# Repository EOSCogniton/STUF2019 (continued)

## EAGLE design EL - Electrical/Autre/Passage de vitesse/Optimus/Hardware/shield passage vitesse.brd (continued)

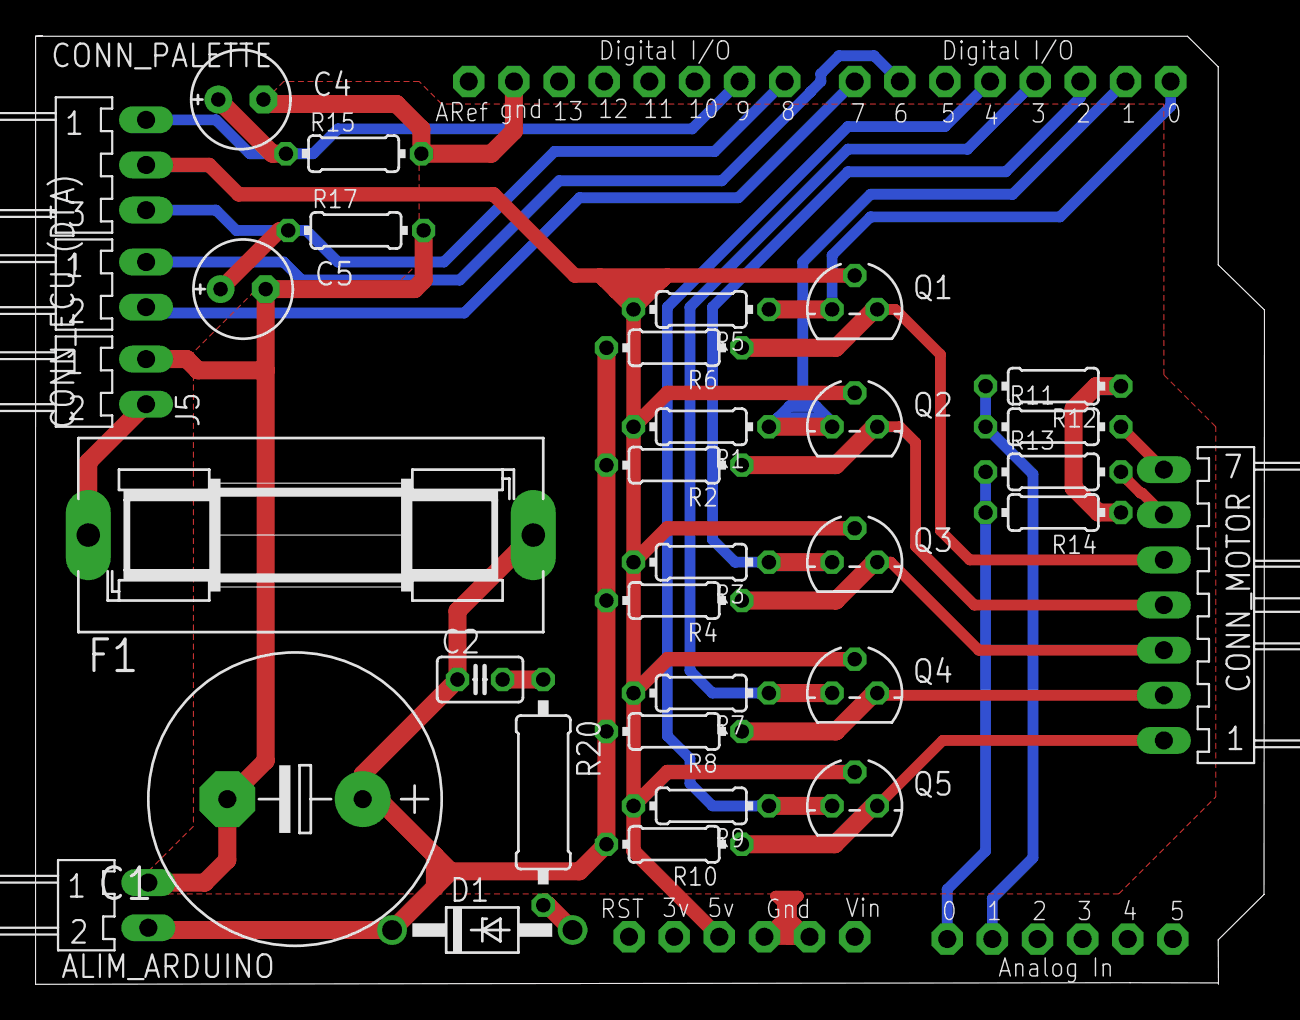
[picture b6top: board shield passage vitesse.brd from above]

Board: 2 copper layers, 69.2 x 53.4 mm, 37 parts (0 on the bottom side), 23 nets.

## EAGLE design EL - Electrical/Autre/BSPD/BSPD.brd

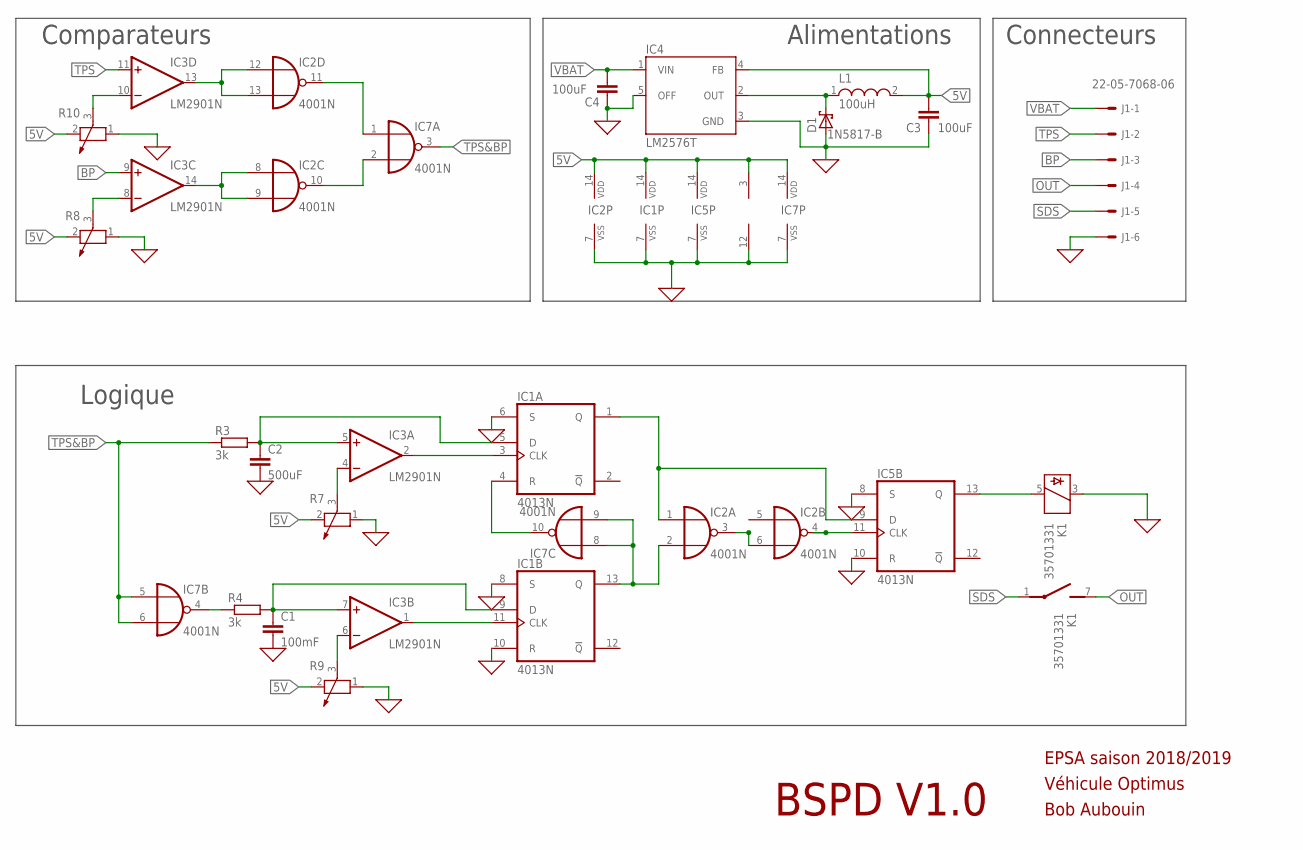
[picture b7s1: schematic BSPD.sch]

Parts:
C1: 100mF; C025-025X050
C2: 500uF; C025-025X050
C3, C4: 100uF; C025-025X050
D1: 1N5817-B; DO41-7.6
IC1, IC5: 4013N; DIL14
IC2, IC7: 4001N; DIL14
IC3: LM2901N; DIL14
IC4: LM2576T; TO220-5
J1: 22-05-7068-06; 7395-06
K1: 35701331; REED
L1: 100uH; WE-TI_8012
R3, R4: 3k; 0204/7
R7, R8, R9, R10: POTENTIOMETER_PT_SPIN; PT-SPIN

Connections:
0: C1.2, C2.2, C3.1, C4.1, D1.A, IC1.6 (S), IC1.7 (VSS), IC1.8 (S), IC1.10 (R), IC2.7 (VSS), IC3.12 (V-), IC4.3 (GND), IC4.5 (OFF), IC5.7 (VSS), IC5.8 (S), IC5.10 (R), IC7.7 (VSS), J1.6, K1.3, R7.1, R8.1, R9.1, R10.1
5V: C3.2, IC1.14 (VDD), IC2.14 (VDD), IC3.3 (V+), IC4.4 (FB), IC5.14 (VDD), IC7.14 (VDD), L1.2, R7.2, R8.2, R9.2, R10.2
BP: IC3.9 (+IN), J1.3
unnamed: C2.1, IC1.5 (D), IC3.5 (+IN), R3.2
unnamed: IC3.4 (-IN), R7.3
unnamed: C1.1, IC1.9 (D), IC3.7 (+IN), R4.2
unnamed: IC3.6 (-IN), R9.3
unnamed: IC1.11 (CLK), IC3.1 (OUT)
unnamed: IC1.3 (CLK), IC3.2 (OUT)
unnamed: IC2.12 (I0), IC2.13 (I1), IC3.13 (OUT)
unnamed: IC1.13 (Q), IC2.2 (I1), IC7.8 (I0), IC7.9 (I1)
unnamed: IC1.1 (Q), IC2.1 (I0), IC5.9 (D)
unnamed: IC2.4 (O), IC5.11 (CLK)
unnamed: IC7.4 (O), R4.1
unnamed: IC5.13 (Q), K1.5
unnamed: IC3.10 (-IN), R10.3
unnamed: IC3.8 (-IN), R8.3
unnamed: IC2.8 (I0), IC2.9 (I1), IC3.14 (OUT)
unnamed: D1.C, IC4.2 (OUT), L1.1
unnamed: IC2.11 (O), IC7.1 (I0)
unnamed: IC2.10 (O), IC7.2 (I1)
unnamed: IC2.3 (O), IC2.5 (I0), IC2.6 (I1)
unnamed: IC1.4 (R), IC7.10 (O)
OUT: J1.4, K1.7 (S)
SDS: J1.5, K1.1
TPS: IC3.11 (+IN), J1.2
TPS&BP: IC7.3 (O), IC7.5 (I0), IC7.6 (I1), R3.1
VBAT: C4.2, IC4.1 (VIN), J1.1

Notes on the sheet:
BSPD V1.0
EPSA saison 2018/2019
Véhicule Optimus
Bob Aubouin
Logique
Comparateurs
Alimentations
Connecteurs

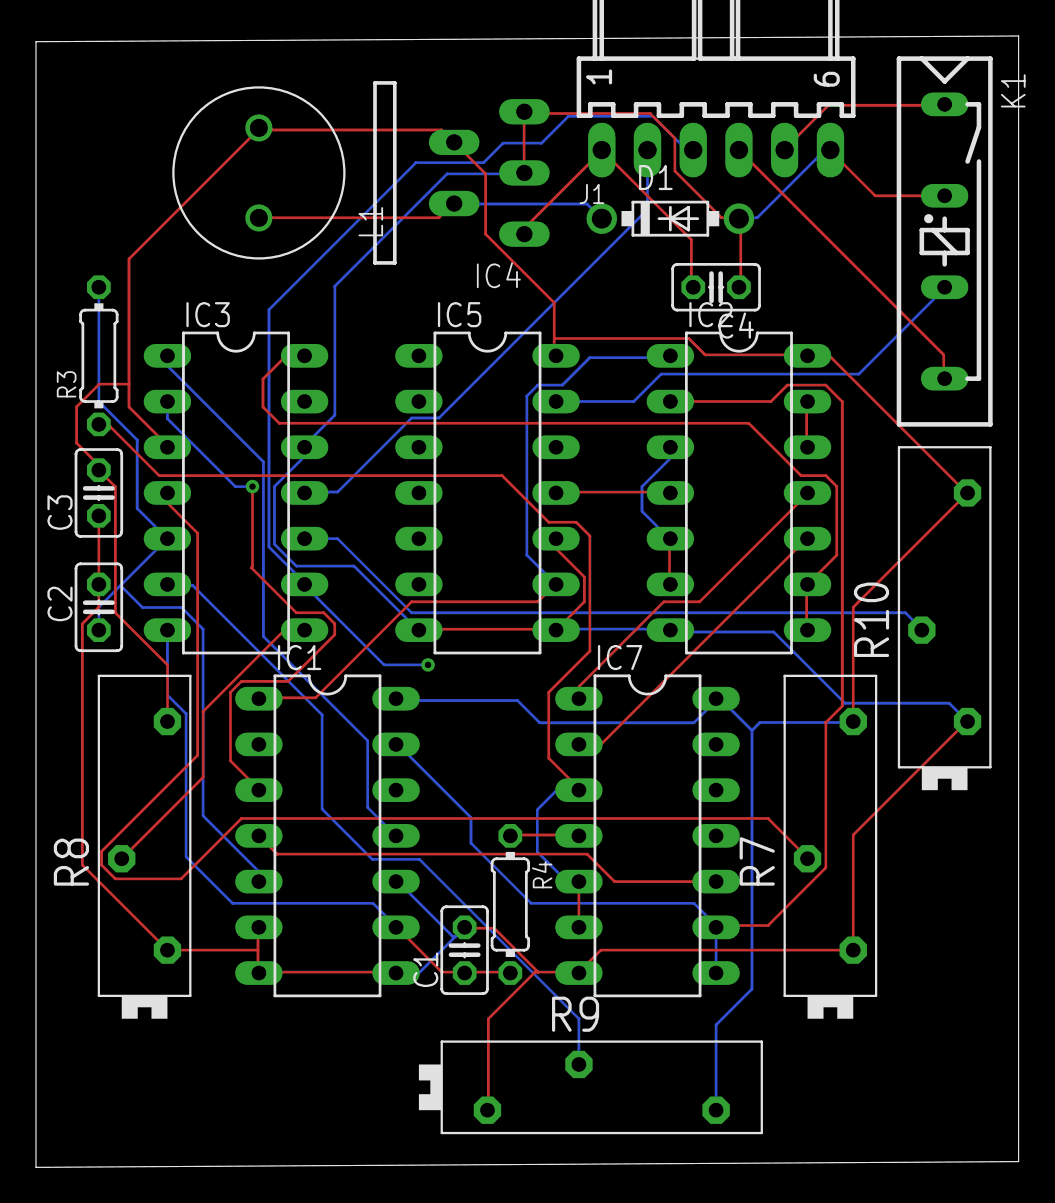
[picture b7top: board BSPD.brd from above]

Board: 2 copper layers, 54.6 x 62.9 mm, 20 parts (0 on the bottom side), 28 nets.

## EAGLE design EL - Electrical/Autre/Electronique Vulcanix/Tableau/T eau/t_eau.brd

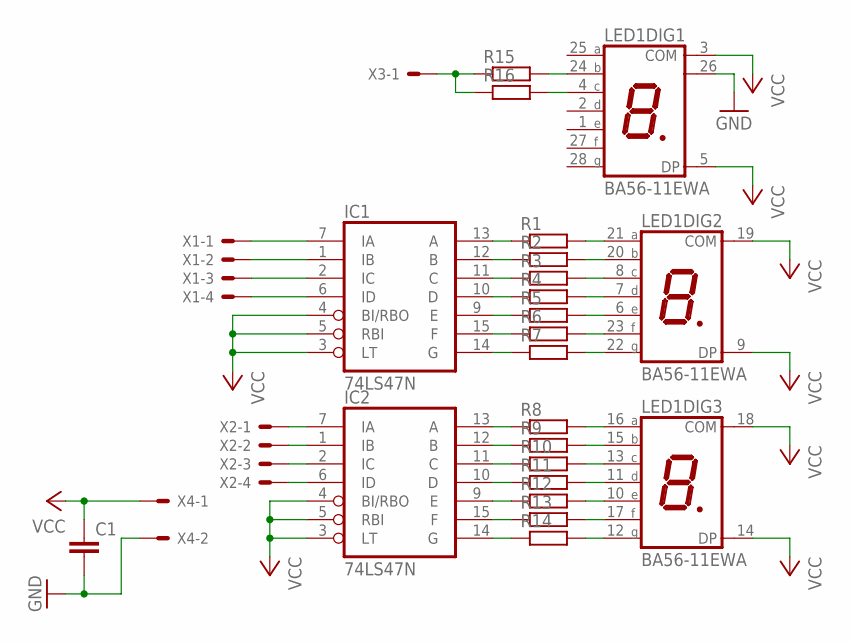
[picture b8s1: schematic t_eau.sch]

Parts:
C1: C-EU025-025X050; C025-025X050
IC1, IC2: 74LS47N; DIL16
LED1: BA56-11EWA; BA/BC56
R1, R2, R3, R4, R5, R6, R7, R8, R9, R10, R11, R12, R13, R14, R15, R16: R-EU_0204/7; 0204/7
X1, X2: KK-156-7
X3, X4: KK-156-2

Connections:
GND: C1.2, IC1.8 (GND), IC2.8 (GND), LED1.26 (COM), X4.2
unnamed: LED1.21 (A), R1.2
unnamed: IC1.12 (B), R2.1
unnamed: IC1.11 (C), R3.1
unnamed: IC1.10 (D), R4.1
unnamed: IC1.9 (E), R5.1
unnamed: IC1.15 (F), R6.1
unnamed: IC1.14 (G), R7.1
unnamed: IC2.13 (A), R8.1
unnamed: IC2.12 (B), R9.1
unnamed: IC2.11 (C), R10.1
unnamed: IC2.10 (D), R11.1
unnamed: IC2.9 (E), R12.1
unnamed: IC2.15 (F), R13.1
unnamed: IC2.14 (G), R14.1
unnamed: IC1.13 (A), R1.1
unnamed: LED1.12 (G), R14.2
unnamed: LED1.17 (F), R13.2
unnamed: LED1.10 (E), R12.2
unnamed: LED1.11 (D), R11.2
unnamed: LED1.13 (C), R10.2
unnamed: LED1.15 (B), R9.2
unnamed: IC1.7 (IA), X1.1
unnamed: IC1.1 (IB), X1.2
unnamed: IC1.2 (IC), X1.3
unnamed: IC1.6 (ID), X1.4
unnamed: LED1.16 (A), R8.2
unnamed: LED1.22 (G), R7.2
unnamed: LED1.23 (F), R6.2
unnamed: LED1.6 (E), R5.2
unnamed: LED1.7 (D), R4.2
unnamed: LED1.8 (C), R3.2
unnamed: LED1.4 (C), R16.2
unnamed: LED1.24 (B), R15.2
unnamed: LED1.20 (B), R2.2
unnamed: IC2.7 (IA), X2.1
unnamed: IC2.1 (IB), X2.2
unnamed: IC2.2 (IC), X2.3
unnamed: IC2.6 (ID), X2.4
unnamed: R15.1, R16.1, X3.1
VCC: C1.1, IC1.3 (LT), IC1.4 (BI/RBO), IC1.5 (RBI), IC1.16 (VCC), IC2.3 (LT), IC2.4 (BI/RBO), IC2.5 (RBI), IC2.16 (VCC), LED1.3 (COM), LED1.5 (DP), LED1.9 (DP), LED1.14 (DP), LED1.18 (COM), LED1.19 (COM), X4.1

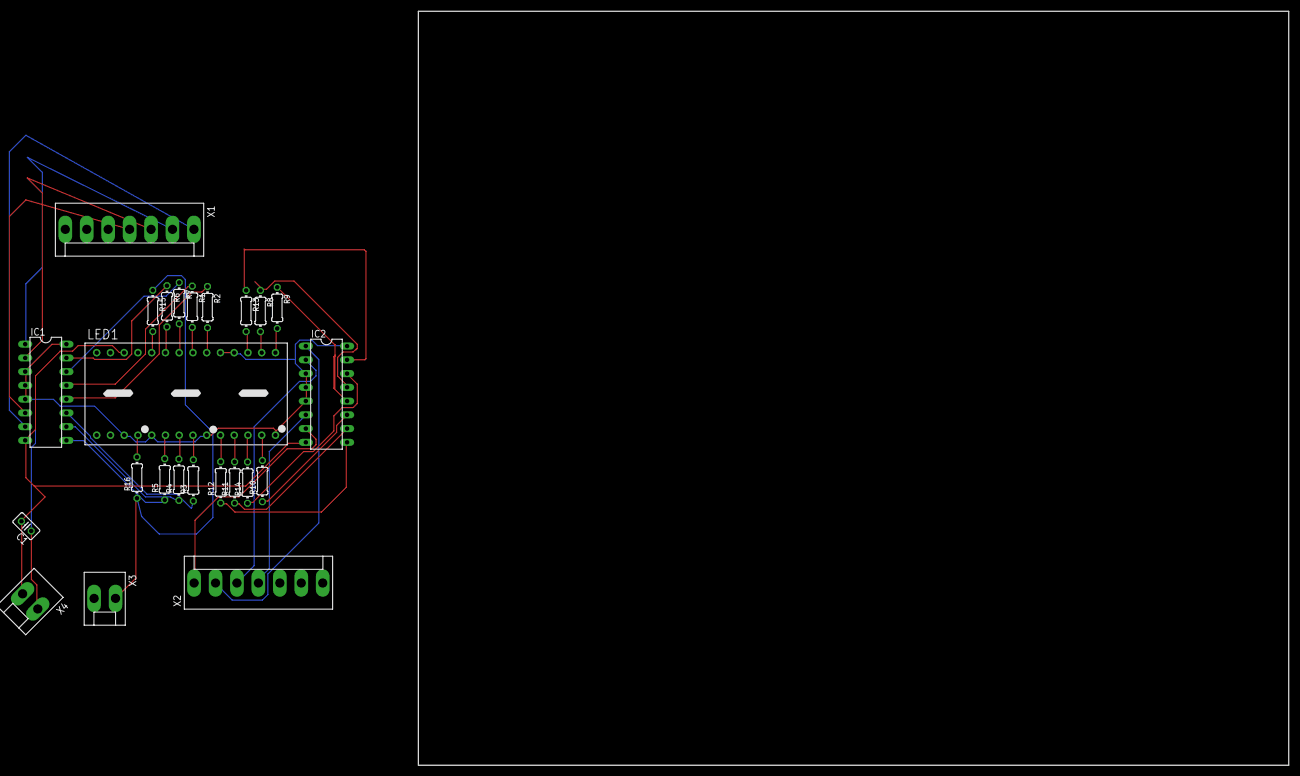
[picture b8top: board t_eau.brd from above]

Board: 2 copper layers, 160.8 x 139.3 mm, 24 parts (0 on the bottom side), 41 nets.

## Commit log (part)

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2019-04-21 devis
2019-04-22 Cost
2019-04-24 Faisceau
2019-04-25 SES à compléter
2019-04-25 tdb modele catia update
2019-04-29 Changement Tube plié PE
2019-04-29 Changement Tube plié PE v2
2019-04-30 modif crise chassis chape basculeur
2019-04-30 problème de collisions crise chassis
2019-04-30 plus de collisions crise chassis
2019-04-30 Chape PE
2019-04-30 Ajouts documents design
2019-05-01 Deivs et elec
2019-05-01 modif
2019-05-01 Cost ajouts
2019-05-01 Mise en page templates
2019-05-01 Crise Chassis supports
2019-05-01 serigraphie
2019-05-01 BOM pédalier + petit coucou de guyane
2019-05-02 carte avant
2019-05-02 Crise chassis tous les tubes
2019-05-04 BOM v1 MS, à faire verif par MPL
2019-05-05 BOM Fuel System
2019-05-05 Cost mise en place fasteners,...
2019-05-05 BOM frame
2019-05-05 Masse elec update
2019-05-05 Processes cost
2019-05-05 BOM brake system
2019-05-05 nouveau gabarit
2019-05-05 WT assy BOM for cost report
    not completed, asked PA for info
2019-05-05 Un peu de tout
2019-05-05 pôle elec à 9kg qui dit mieux ?
2019-05-06 Renforts chassis fichiers simu DESIGN
2019-05-06 WT MEP folder update
    for cost design
2019-05-06 WT BOM pics and meps
2019-05-06 WT BOM cost design report
    pics and meps finalization, BOM update for speed sensor position parts
2019-05-06 Ajouts ressources design report
2019-05-06 CR drivetrain
2019-05-06 BOM TS
2019-05-06 BOM Clutch actuation
2019-05-07 cost chapes
2019-05-07 Fin maillage chassis design <3
2019-05-07 Cost fasteners
2019-05-07 capteur
2019-05-07 WT BOM data
    frette de frein, roulements data
2019-05-07 WT BOM cost design
    ecrous, goujons, ecrous de serrage, tripod, ecrou tripod, rondelles encoche
2019-05-08 cost arb parts
2019-05-08 maj faisceau et c'est pas finis
2019-05-08 cost maj
2019-05-08 Maj coost
2019-05-08 COst clutch actuation system
2019-05-08 BOM_Tsec
2019-05-08 Modif Cost MS+ Finalisation Pare Feu
2019-05-09 Cost direction GTE
2019-05-09 Ajout image assemblage + conversion
2019-05-09 Changement de nomenclature
2019-05-09 Tsec
2019-05-10 cost bracket
2019-05-11 BOM Ftank
2019-05-11 Cost MS, ergo mal rangé/pas fini ptin
2019-05-11 Cost MS v2
2019-05-11 Rangement MS
2019-05-11 Cost MS v3
2019-05-11 cost body et fond plat
2019-05-11 WT BOM cost report
    il manque encor la MEP de la piste capteur de vitesse ( WT_03006)
2019-05-11 WT BOM cost report
    MEP piste acier capteur vitesse
2019-05-11 EL BOM cost report
2019-05-11 BOM Engine
2019-05-12 MAJ BOM Engine
2019-05-12 cost SU
2019-05-12 Picture BOM
2019-05-12 BOM Engine okay
2019-05-12 Modif oublié de push cost
2019-05-12 EL BOM cost report update
2019-05-12 Ajout photo brackets steering + cache-crémaillère
2019-05-12 Petite modif
2019-05-13 Cost in progress
2019-05-13 WT BOM excel update
2019-05-13 Maj Bom Déso
2019-05-13 Modif légère Cost
2019-05-14 plans chassis
2019-05-14 cost BOM frame chapes
2019-05-14 modif capteur
2019-05-15 CR EL : excel et premieres images
2019-05-15 BOM steering
2019-05-15 EL BOM rename pictures
2019-05-15 BOM triangles
2019-05-15 BOM biellettes
2019-05-15 Correction BOM WT
2019-05-15 capt
2019-05-15 Chapes LAS Cost
2019-05-15 Correction SU PAT
2019-05-15 Correction MS
2019-05-15 Correction BR erwan
2019-05-15 Correction engine motor + overflow bottles
2019-05-15 Correction EN CEE
2019-05-15 test
2019-05-15 Voila mon ami Reedom
2019-05-15 Update EL BOM plus d'image
2019-05-15 BOM brake
2019-05-16 Fin BOM MS
2019-05-17 Corrections cost
2019-05-17 jacking bar cost
2019-05-17 chapes moteur COST
2019-05-17 ajout
2019-05-18 BOM SU_1000 et SU_11000
    pas des spacer car --> triangles
2019-05-18 BOM SU_1000 et SU_11000
    il manque le nombre de cales de carrossage
2019-05-18 Update BOM EL, ajout images
2019-05-19 BOM SU and bearing preload
    to find out
2019-05-19 BOM EL dernières img, verif nom+taille img
2019-05-19 update BOM brake system
2019-05-19 Fuel System BOM
2019-05-19 Images bom br
2019-05-20 Ajout de la VSV en low quality pour les juges
2019-05-20 VSV raccourci
2019-05-20 Simulations design résolution bordel
2019-05-21 Business plan + chassis surfacique DS
2019-05-21 Correction BR 1 / 2
2019-05-21 Correction EN + oublie soufflets steering
2019-05-21 Correction EN
2019-05-21 Cost Cooling
2019-05-21 Correction EN cooling
2019-05-21 BOM SU
2019-05-21 Correction Br
2019-05-21 Correction SU
2019-05-21 Correction Frame cost
2019-05-22 un max de truc
2019-05-22 Maj pedals cost
2019-05-22 Correction EN intake system
2019-05-22 BOM quasi fini
2019-05-22 Cost model
2019-05-22 modif carte avant
2019-05-22 Frame encule le Design Report
2019-05-22 image clutch actution system
2019-05-23 Cost report benji
2019-05-23 Cost mise en forme DBOM
2019-05-23 Modif BOM
2019-05-23 Le cost c'est fun
2019-05-23 DBOM ça part
2019-05-24 BOM WT SU assembly
    images des assemblages
2019-05-24 BOM WT brake discs
2019-05-25 BP an dernier
2019-05-25 Executive summary
2019-05-26 Avancée modèle coût
2019-05-26 Premiers prix pour CNC mill
2019-05-26 Une Ref erronée sur BOM MS
2019-05-27 Ca va être long
2019-05-28 Cost - yeah
2019-05-29 On aide Robin pour le Design
2019-05-29 DR Simu Chassis Fond Blanc
2019-05-29 BP plus COST
2019-05-29 MAJ design
2019-05-30 Fuel system DBOM
2019-05-30 Update cost
2019-05-30 proto chainshield
2019-05-30 début DBOM BR
2019-05-31 Maj excel fasteners, processes, ...
2019-05-31 Cost Br_A0100
2019-05-31 modif Br_A0100
2019-06-01 cost Br_A0200
2019-06-02 DBOM
2019-06-02 Executive summary sur le git pour tous
2019-06-02 Design support chassis
2019-06-02 Notes BOM ELEC
2019-06-04 skf detail
2019-06-04 DBOM ENGINE
2019-06-04 DESO MAJ DBOM ENGINE
2019-06-04 COst correction
2019-06-05 Analyse Frame
2019-06-05 BOM FR
2019-06-05 Cost update
2019-06-05 DBOM FTank
2019-06-06 ftank dbom
2019-06-07 Design support frame
2019-06-08 sight tube
2019-06-09 mesure moyeu
2019-06-09 cost moteur + carte avant
2019-06-10 DBOM T
2019-06-10 Cost report update
2019-06-10 cost EL update
2019-06-11 Cost FR
2019-06-11 MAJ BOM EN
2019-06-11 MAJ BOM EN 2
2019-06-11 Modif MEP et ajout CNC lathe
2019-06-11 maj dbom br
2019-06-12 MAJ BOM EN 3
2019-06-12 Conversation sylvain soudure
2019-06-12 update BR0100
2019-06-13 Cost FR_0200
2019-06-13 photo pour cost
2019-06-15 Modif cost BR
2019-06-16 Passage HT
2019-06-16 Corrections DBOM
2019-06-16 Creation dossier pictures
2019-06-16 DS wheels and tires
2019-06-16 dbom cooling
2019-06-16 modele
2019-06-16 Correction DBOM
2019-06-16 correction cooling
2019-06-16 correction ftank
2019-06-16 FTank
2019-06-16 cooling
2019-06-16 Chainshield
2019-06-16 pedal
2019-06-17 Mise en place cout assemblages
2019-06-17 Modifs cost model
2019-06-17 fin des chapes
2019-06-17 MAJ DBOM
2019-06-17 correction cost br
2019-06-17 again
2019-06-17 pedal cost
2019-06-17 Modification de la macro cost report : ajout images automatique, ajout de lien automatique
2019-06-18 DBOM steering
2019-06-18 Modifs materiaux cost
2019-06-18 MAJ DBOM ENGINE
2019-06-18 Ajout colle
2019-06-18 push push push
2019-06-18 Update cost yeah
2019-06-19 master switch
2019-06-19 Update cost again
2019-06-19 Modif MS
2019-06-19 push
2019-06-19 Maj processe cost
2019-06-19 Document
2019-06-19 DS frame
2019-06-19 BP et design
2019-06-20 BP et DS
2019-06-21 Updateee
2019-06-21 push!
2019-06-21 Cost updateee
2019-06-21 DS_Elec
2019-06-21 Maj cost
2019-06-21 Simu Design FRAME
2019-06-21 Preparation oral cost
2019-06-21 Sight tube model
2019-06-25 ajout matrice data logger DS elec
2019-06-25 Appuie tête
2019-06-26 Design report A-Arms
2019-06-26 Design report triangles
2019-06-26 Maj code carte avant
2019-06-27 Mise en forme cost
2019-07-01 Ajout Test Frame pour DS
2019-07-03 bails pas à jour
2019-07-03 modif faisceau code carte avant
2019-07-03 Challah les simulations qui vont marcher bientot
2019-07-03 pareil
2019-07-03 Cost preparation oral
2019-07-03 SIMUS FRAME POUTRE CA MARCHE
    5/8 simus
2019-07-04 SIMUS FRAME POUTRE 2
2019-07-04 Cost oral presentation
2019-07-05 Cost oral preparation
2019-07-05 Maj oral cost
2019-07-05 Oral
2019-07-14 Préparation oral FS ATA
2019-07-14 Oral cost
2019-07-14 simulations
2019-07-14 preparation fsata
2019-07-14 prepar FSATA
2019-07-17 prepar FSATA2
2019-07-21 Cost oral
2019-07-22 Affiches cost
2019-08-03 Remise en forme dossier cost
2019-09-25 Test symlink
2019-10-11 Ajout Stoca
